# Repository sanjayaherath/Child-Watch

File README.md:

# Child-Watch

## Introduction ##

This project was developed for EE356-Electronic Product Design and Manufacture Project. A market ready prototype of a child watch was developed.

**Group Members:** [Sanjaya Herath](https://sanjayaherath.github.io/), [Yasiru Ranasinghe](https://www.researchgate.net/profile/Don_Yasiru_Ranasinghe), and [Anupamali Willamuna](https://www.linkedin.com/in/anupamali-willamuna-0743a11a4/?originalSubdomain=lk).

**Supervised by:** [Dr. Janaka Wijayakulasooriya](http://eng.pdn.ac.lk/deee/staff/academic/dr.j.wijayakulasooriya/profile.php), [Dr. Ruwan Ranaweera ](http://eng.pdn.ac.lk/pages/departmentHome/EE/otherpages/staff/rdbranaweera.html), and [Dr. Uditha Navaratne](http://eng.pdn.ac.lk/deee/staff/academic/mr.us.navaratne/profile.php)

## Project Overview ##

The firmware was developed using arduino and PCBs were designed using Eagle CAD. The main components of hardware were arduino pro mini, OLED display, and sim800l.
The child watch includes features such as send and receive a specific number of messages, digital clock, stop watch and recieve notifications through vibrations.

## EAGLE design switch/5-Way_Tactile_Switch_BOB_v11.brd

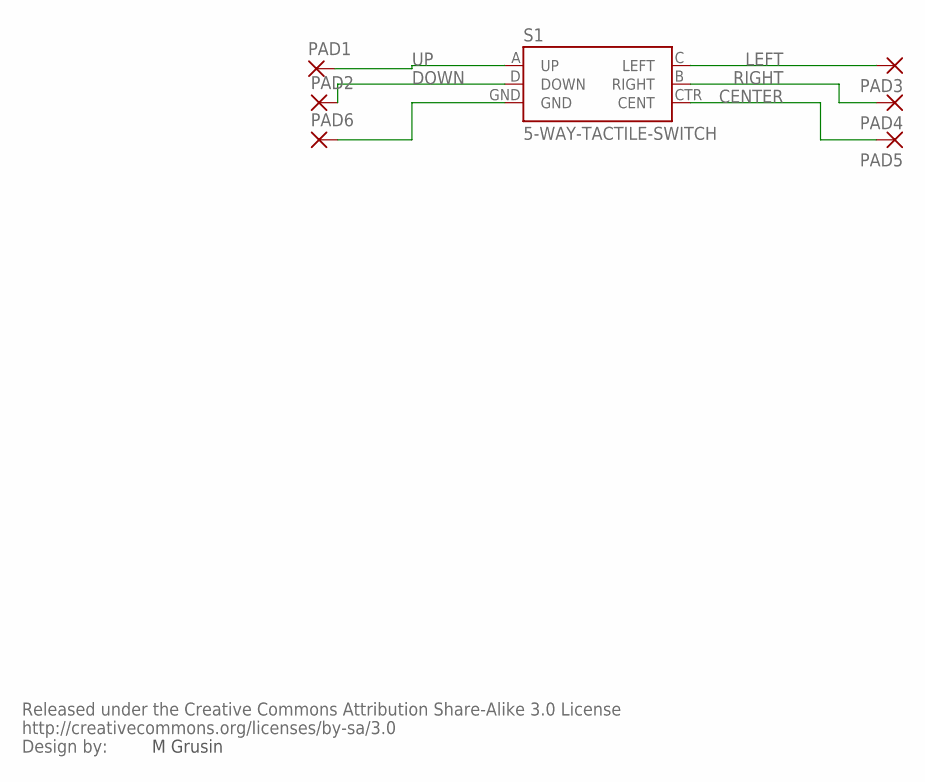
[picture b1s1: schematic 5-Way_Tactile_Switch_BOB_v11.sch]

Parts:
PAD1, PAD2, PAD3, PAD4, PAD5, PAD6: SMD2; SMD1,27-2,54
S1: 5-WAY-TACTILE-SWITCH; JOYSTICK_MINI
U$2: CREATIVE_COMMONS

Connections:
CENTER: PAD5.1, S1.CTR (CENT)
DOWN: PAD2.1, S1.D (DOWN)
GND: PAD6.1, S1.GND
LEFT: PAD3.1, S1.C (LEFT)
RIGHT: PAD4.1, S1.B (RIGHT)
UP: PAD1.1, S1.A (UP)

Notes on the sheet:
M Grusin

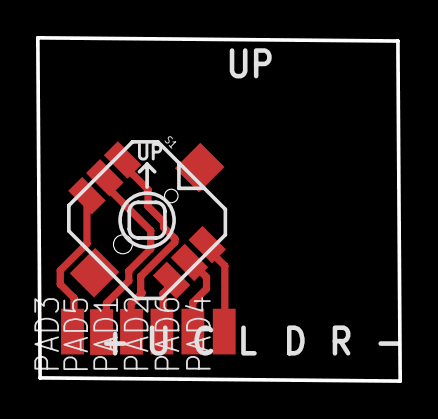
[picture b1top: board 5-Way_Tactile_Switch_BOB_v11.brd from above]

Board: 2 copper layers, 20.1 x 19.1 mm, 8 parts (0 on the bottom side), 6 nets.

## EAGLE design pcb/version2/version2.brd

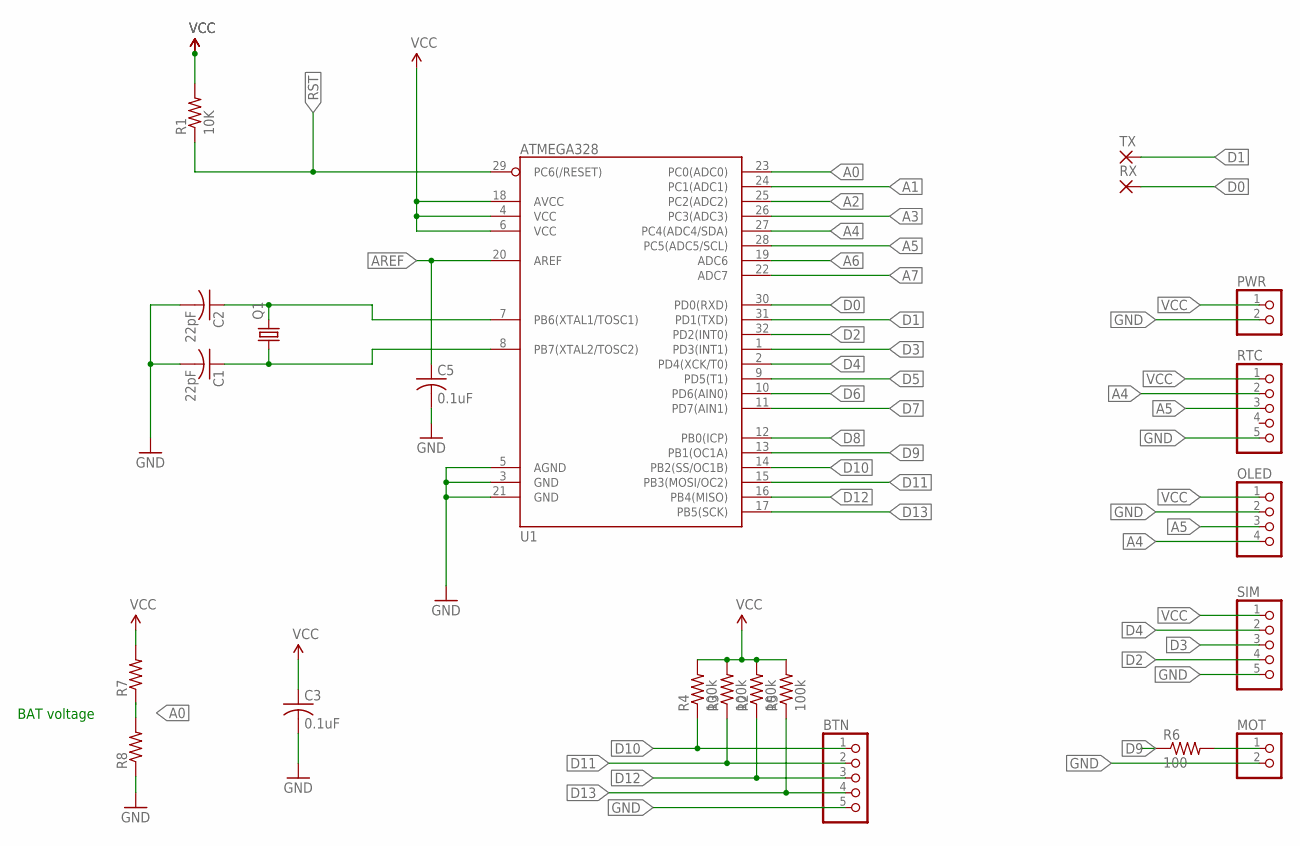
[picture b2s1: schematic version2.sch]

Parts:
BTN: PINHD-1X5; 1X05
C1, C2: 22pF; C1206
C3, C5: 0.1uF; C0805
MOT: PINHD-1X2; 1X02
OLED: PINHD-1X4; 1X04
PWR: PINHD-1X2; 1X02
Q1: CRYSTALHC18U-V; HC18U-V
R1: 10K; R0805
R2, R3, R4, R5: 100k; R0805
R6: 100; R0805
R7, R8: R-US_R0805; R0805
RTC: PINHD-1X5; 1X05
RX: SMD2; SMD1,27-2,54
SIM: PINHD-1X5; 1X05
TX: SMD2; SMD1,27-2,54
U1: ATMEGA328; TQFP32-08

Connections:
A0: R7.1, R8.2, U1.23 (PC0(ADC0))
A1: U1.24 (PC1(ADC1))
A2: U1.25 (PC2(ADC2))
A3: U1.26 (PC3(ADC3))
A4: OLED.4, RTC.2, U1.27 (PC4(ADC4/SDA))
A5: OLED.3, RTC.3, U1.28 (PC5(ADC5/SCL))
A6: U1.19 (ADC6)
A7: U1.22 (ADC7)
AREF: C5.1, U1.20 (AREF)
D0: RX.1, U1.30 (PD0(RXD))
D1: TX.1, U1.31 (PD1(TXD))
D2: SIM.4, U1.32 (PD2(INT0))
D3: SIM.3, U1.1 (PD3(INT1))
D4: SIM.2, U1.2 (PD4(XCK/T0))
D5: U1.9 (PD5(T1))
D6: U1.10 (PD6(AIN0))
D7: U1.11 (PD7(AIN1))
D8: U1.12 (PB0(ICP))
D9: R6.1, U1.13 (PB1(OC1A))
D10: BTN.1, R4.1, U1.14 (PB2(SS/OC1B))
D11: BTN.2, R3.1, U1.15 (PB3(MOSI/OC2))
D12: BTN.3, R2.1, U1.16 (PB4(MISO))
D13: BTN.4, R5.1, U1.17 (PB5(SCK))
GND: BTN.5, C1.2, C2.2, C3.2, C5.2, MOT.2, OLED.2, PWR.2, R8.1, RTC.5, SIM.5, U1.3 (GND), U1.5 (AGND), U1.21 (GND)
unnamed: MOT.1, R6.2
unnamed: C2.1, Q1.2, U1.7 (PB6(XTAL1/TOSC1))
unnamed: C1.1, Q1.1, U1.8 (PB7(XTAL2/TOSC2))
RST: R1.1, U1.29 (PC6(/RESET))
VCC: C3.1, OLED.1, PWR.1, R1.2, R2.2, R3.2, R4.2, R5.2, R7.2, RTC.1, SIM.1, U1.4 (VCC), U1.6 (VCC), U1.18 (AVCC)

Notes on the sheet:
BAT voltage

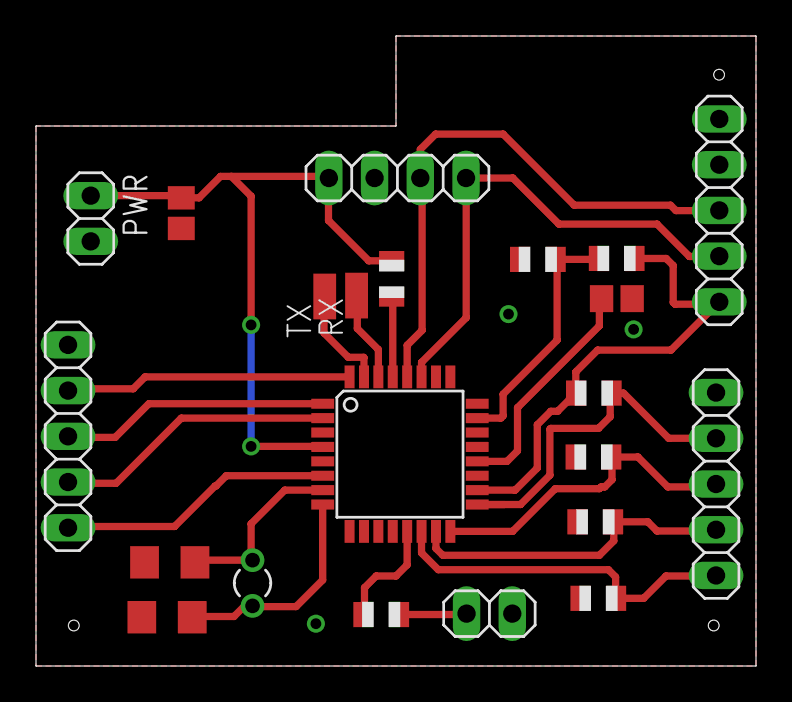
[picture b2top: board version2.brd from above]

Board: 2 copper layers, 40.0 x 35.0 mm, 22 parts (0 on the bottom side), 20 nets.

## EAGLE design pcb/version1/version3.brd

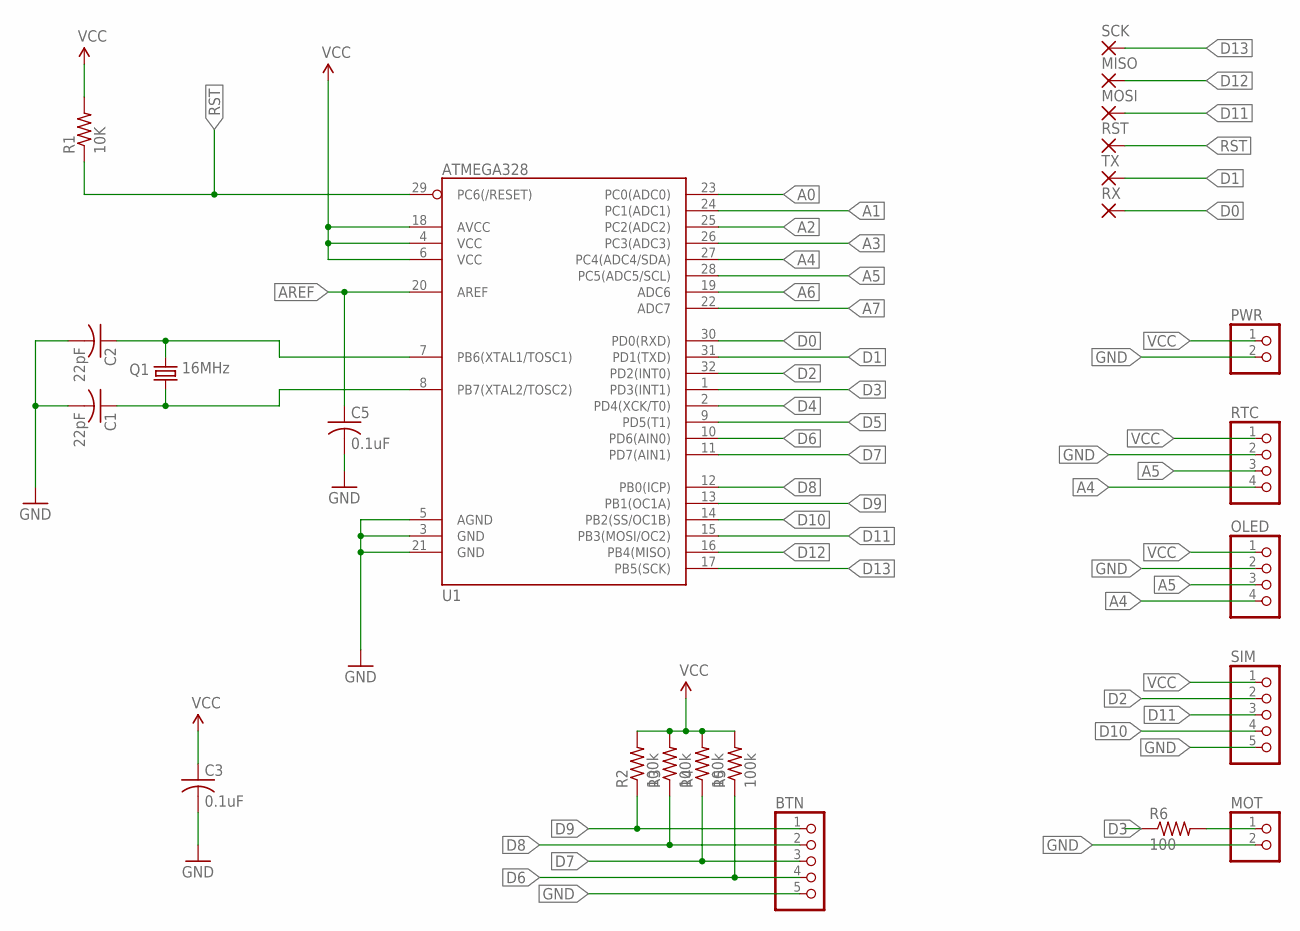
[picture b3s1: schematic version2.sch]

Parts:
BTN: PINHD-1X5; 1X05
C1, C2: 22pF; C1206
C3, C5: 0.1uF; C0805
MISO: SMD2; SMD1,27-2,54
MOSI: SMD2; SMD1,27-2,54
MOT: PINHD-1X2; 1X02
OLED: PINHD-1X4; 1X04
PWR: PINHD-1X2; 1X02
Q1: 16MHz; TC26V
R1: 10K; R1206
R2, R3, R4, R5: 100k; R1206
R6: 100; R1206
RST: SMD2; SMD1,27-2,54
RTC: PINHD-1X4; 1X04
RX: SMD2; SMD1,27-2,54
SCK: SMD2; SMD1,27-2,54
SIM: PINHD-1X5; 1X05
TX: SMD2; SMD1,27-2,54
U1: ATMEGA328; TQFP32-08

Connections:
A0: U1.23 (PC0(ADC0))
A1: U1.24 (PC1(ADC1))
A2: U1.25 (PC2(ADC2))
A3: U1.26 (PC3(ADC3))
A4: OLED.4, RTC.4, U1.27 (PC4(ADC4/SDA))
A5: OLED.3, RTC.3, U1.28 (PC5(ADC5/SCL))
A6: U1.19 (ADC6)
A7: U1.22 (ADC7)
AREF: C5.1, U1.20 (AREF)
D0: RX.1, U1.30 (PD0(RXD))
D1: TX.1, U1.31 (PD1(TXD))
D2: SIM.2, U1.32 (PD2(INT0))
D3: R6.1, U1.1 (PD3(INT1))
D4: U1.2 (PD4(XCK/T0))
D5: U1.9 (PD5(T1))
D6: BTN.4, R5.1, U1.10 (PD6(AIN0))
D7: BTN.3, R4.1, U1.11 (PD7(AIN1))
D8: BTN.2, R3.1, U1.12 (PB0(ICP))
D9: BTN.1, R2.1, U1.13 (PB1(OC1A))
D10: SIM.4, U1.14 (PB2(SS/OC1B))
D11: MOSI.1, SIM.3, U1.15 (PB3(MOSI/OC2))
D12: MISO.1, U1.16 (PB4(MISO))
D13: SCK.1, U1.17 (PB5(SCK))
GND: BTN.5, C1.2, C2.2, C3.2, C5.2, MOT.2, OLED.2, PWR.2, RTC.2, SIM.5, U1.3 (GND), U1.5 (AGND), U1.21 (GND)
unnamed: MOT.1, R6.2
unnamed: C2.1, Q1.2, U1.7 (PB6(XTAL1/TOSC1))
unnamed: C1.1, Q1.1, U1.8 (PB7(XTAL2/TOSC2))
RST: R1.1, RST.1, U1.29 (PC6(/RESET))
VCC: C3.1, OLED.1, PWR.1, R1.2, R2.2, R3.2, R4.2, R5.2, RTC.1, SIM.1, U1.4 (VCC), U1.6 (VCC), U1.18 (AVCC)

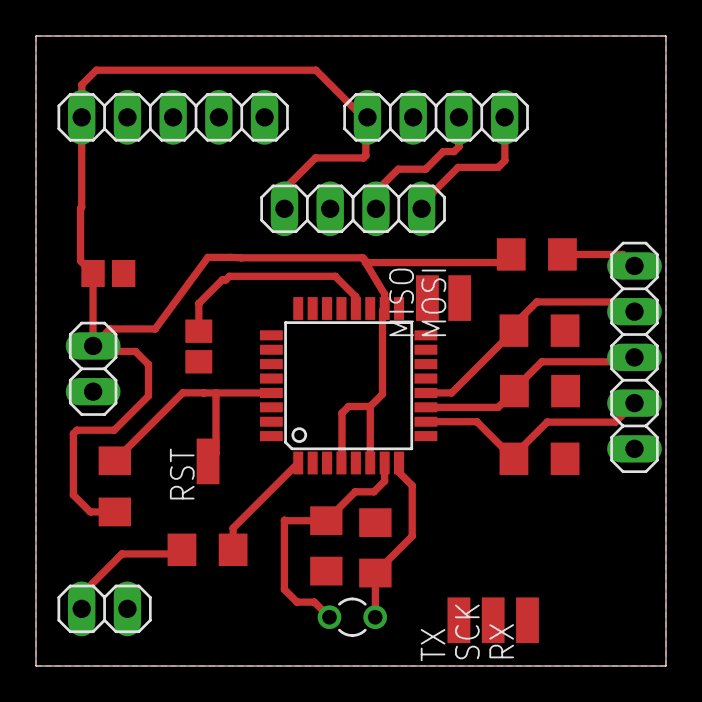
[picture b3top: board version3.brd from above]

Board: 2 copper layers, 35.0 x 35.0 mm, 24 parts (0 on the bottom side), 21 nets.

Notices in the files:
parts and their libraries:
SparkFun: Licensing: CC v3.0 Share-Alike You are welcome to use this library for commercial purposes.
SparkFun: Released under the Creative Commons Attribution Share-Alike 3.0 License
SparkFun: http://creativecommons.org/licenses/by-sa/3.0
